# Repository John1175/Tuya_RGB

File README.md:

# Tuya_RGB

Try1

涂鸦智能【幻彩灯带】Arduino开发

This project is developed using Tuya SDK, which enables you to quickly develop branded apps connecting and controlling smart scenarios of many devices.For more information, please check Tuya Developer Website

The hardware for the project is made by the KiCad.

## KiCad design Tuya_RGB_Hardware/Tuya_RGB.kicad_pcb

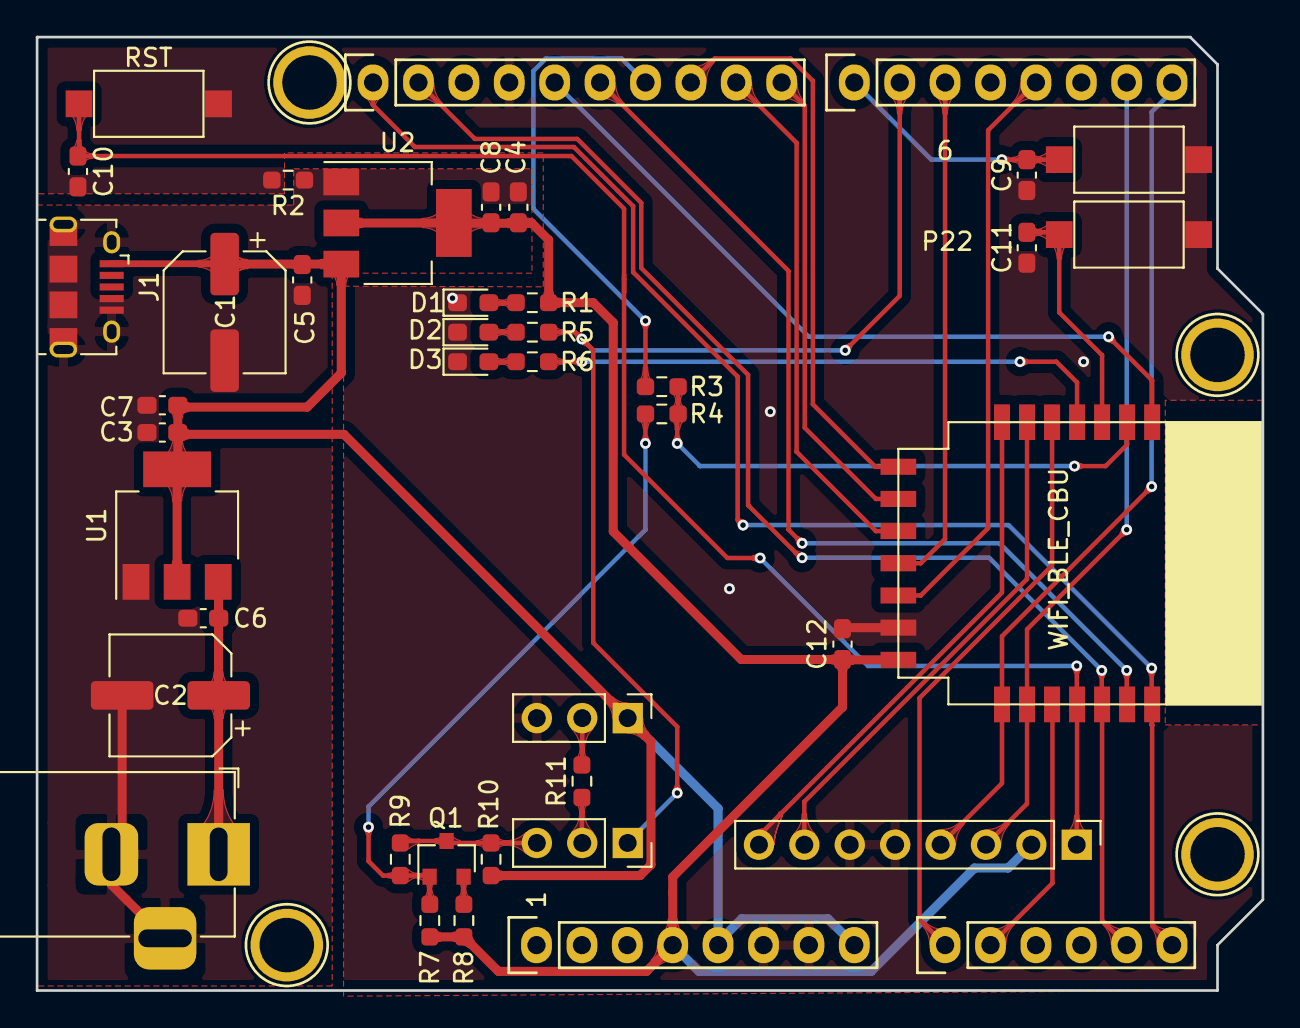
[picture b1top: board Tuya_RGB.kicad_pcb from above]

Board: 2 copper layers, 68.6 x 53.3 mm, 46 parts (0 on the bottom side), 35 nets.

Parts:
C1, C2: 220uF_20%; CP_Elec_6.3x5.8
C3, C4, C5, C6, C9, C10, C11, C12: 0.1uF_20%; C_0603_1608Metric_Pad1.08x0.95mm_HandSolder
C7, C8: 10uF_20%; C_0603_1608Metric_Pad1.08x0.95mm_HandSolder
D1, D2, D3: LED; LED_0603_1608Metric_Pad1.05x0.95mm_HandSolder
J1: USB_B_Micro; USB_Micro-B_Amphenol_10118194_Horizontal
J2: Barrel_Jack_Switch; BarrelJack_Horizontal
J3: Conn_01x03; PinSocket_1x03_P2.54mm_Vertical
J4: Conn_01x08; PinHeader_1x08_P2.54mm_Vertical
J5: Conn_01x03; PinHeader_1x03_P2.54mm_Vertical
P1: Power; Socket_Strip_Arduino_1x08
P2: Analog; Socket_Strip_Arduino_1x06
P3: Digital; Socket_Strip_Arduino_1x10
P4: Digital; Socket_Strip_Arduino_1x08
P5, P6, P7, P8: CONN_01X01; Arduino_1pin
Q1: S8050; SOT-23
R1, R5, R6: 1k_5%; R_0603_1608Metric_Pad0.98x0.95mm_HandSolder
R2, R3: 0R; R_0603_1608Metric_Pad0.98x0.95mm_HandSolder
R4, R9: 0R/NC; R_0603_1608Metric_Pad0.98x0.95mm_HandSolder
R7, R8, R10: 2k_5%; R_0603_1608Metric_Pad0.98x0.95mm_HandSolder
R11: 1R_5%; R_0603_1608Metric_Pad0.98x0.95mm_HandSolder
SW1, SW2, SW3: SW_Push; SW_SPST_CK_RS282G05A3
U1: AMS1117-5.0; SOT-223-3_TabPin2
U2: AMS1117-3.3; SOT-223-3_TabPin2
U3: WIFI_BLE_CBU

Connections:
+3V3: C4.1, C8.1, C12.1, J4.2, P1.4, R1.1, R7.1, R8.1, U2.2, U3.14
+5V: C1.1, C3.1, C5.1, C7.1, J1.1, J5.1, P1.5, P1.8, R10.1, U1.2, U2.3
/0(Rx): J4.4, P4.8, U3.15
/1(Tx): J4.3, P4.7, U3.16
/3(**): P4.5, U3.12
/5(**): P4.3, U3.11
/6(**): J3.1, P4.2, R5.1
/7: C9.1, P4.1, SW1.1
/8: P3.10, U3.9
/9(**): P3.9, U3.10
/10(**/SS): P3.8, U3.8
/11(**/MOSI): P3.7, R4.2
/12(MISO): P3.6, U3.20
/13(SCK): P3.5, U3.1
/A0: P2.1, U3.5
/A1: P2.2, U3.17
/A4(SDA): P2.5, P3.2, U3.19
/A5(SCL): P2.6, P3.1, U3.21
/KEY: C11.1, SW3.1, U3.3
/OUT_DATA: Q1.1, R3.1, R7.2, R9.1
/OUT_RGB_ARD: J3.2, R11.1
/OUT_RGB_CBU: J3.3, Q1.3, R9.2, R10.2
/P16: R3.2, R4.1, U3.2
/P22: R6.1, U3.4
/RST: C10.1, J4.1, SW2.1, U3.18
/RX2: J4.7, U3.6
/TX2: J4.8, U3.7
GND: C9.2, C10.2, C11.2, C12.2, D1.1, D2.1, D3.1, J4.5, J4.6, J5.3, P1.6, P1.7, P3.4, R2.2, SW1.2, SW2.2, SW3.2, U3.13
GNDREF: C1.2, C2.2, C3.2, C4.2, C5.2, C6.2, C7.2, C8.2, J1.4, J1.5, J1.6, J2.2, J2.3, R2.1, U1.1, U2.1
unnamed: D1.2, R1.2
unnamed: D2.2, R5.2
unnamed: D3.2, R6.2
unnamed: J5.2, R11.2
unnamed: Q1.2, R8.2
VCC: C2.1, C6.1, J2.1, U1.3

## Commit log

2021-05-30 The hardware for the project.
2021-05-30 The change of Readme
